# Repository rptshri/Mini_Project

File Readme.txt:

http://www.me.umn.edu/education/undergraduate/writing/How-to-write-a-Design-Report.pdf

ARDUINO DESIGN:
https://www.allaboutcircuits.com/technical-articles/understanding-arduino-uno-hardware-design/

SG90 http://www.ee.ic.ac.uk/pcheung/teaching/DE1_EE/stores/sg90_datasheet.pdf

MG995 https://www.towerpro.com.tw/product/mg995/

BLUETOOTH MODULE  https://howtomechatronics.com/tutorials/arduino/arduino-and-hc-05-bluetooth-module-tutorial/

MDF https://en.wikipedia.org/wiki/Medium-density_fibreboard

3D Design https://www.tinkercad.com/things/dJmnHaHhOIF-grand-snaget-amur/edit

Materials https://www.3dhubs.com/knowledge-base/pla-vs-abs-whats-difference 

MDF Plywood difference https://www.livspace.com/magazine/mdf-vs-plywood-comparison/

1. Project report *
2. Imperial Sheet *
3. Project hardware  *   
4. Project log book *
5. altium pcb file 
6. Proteus simulation file *
7. Pcb vs schematic.  8.Code

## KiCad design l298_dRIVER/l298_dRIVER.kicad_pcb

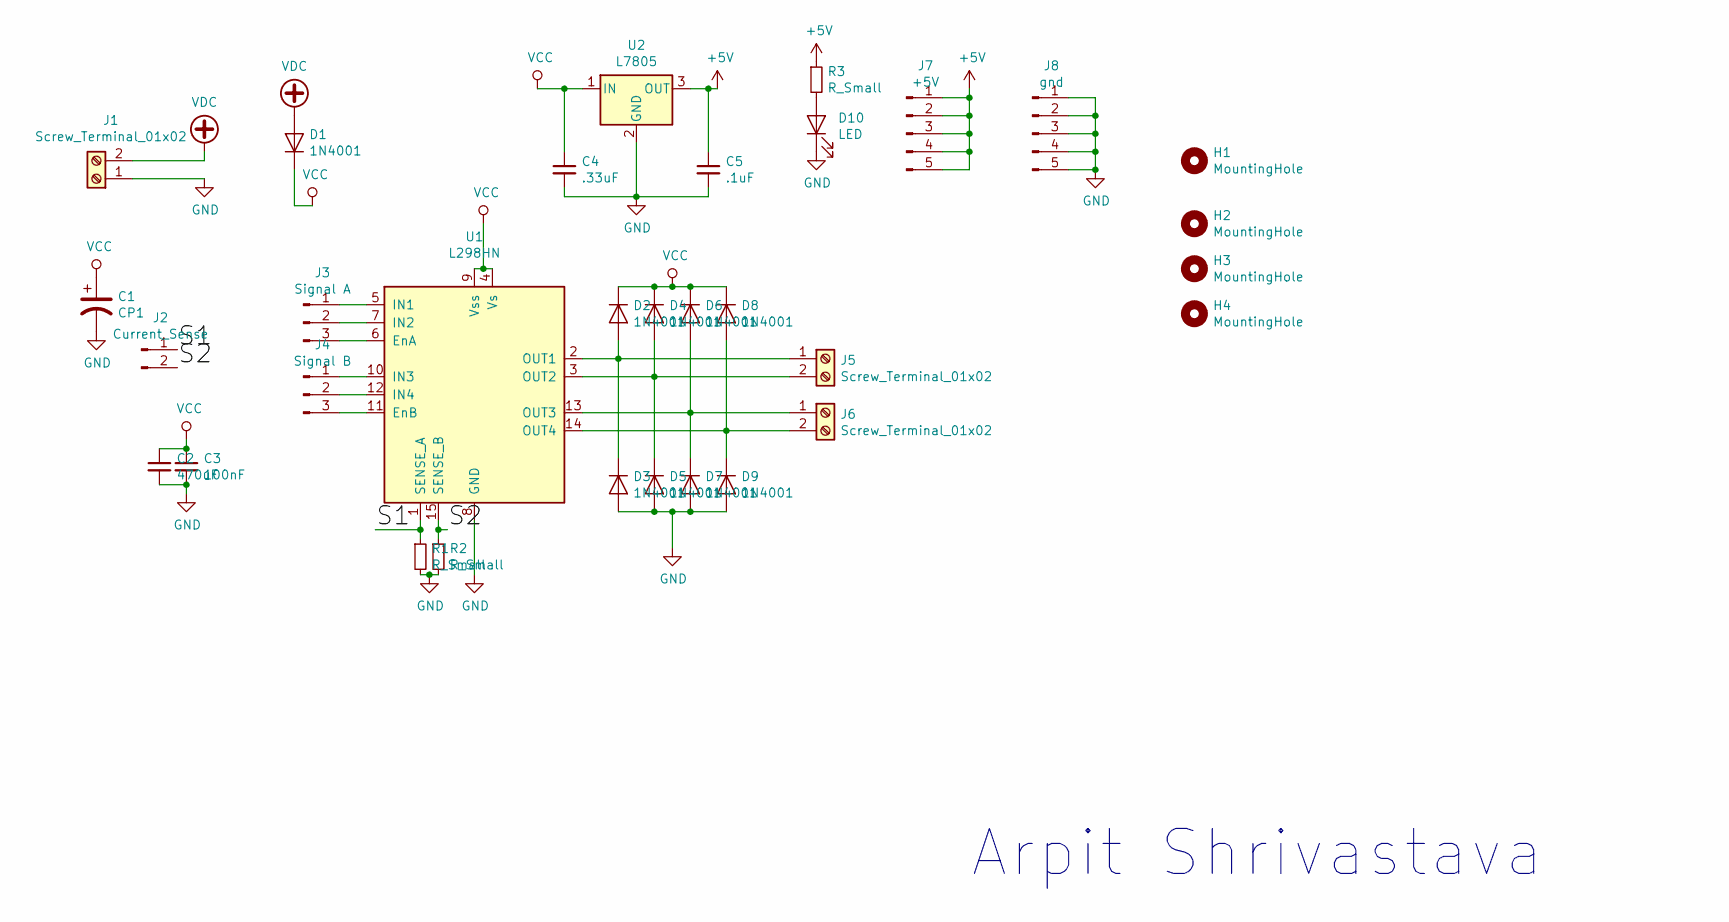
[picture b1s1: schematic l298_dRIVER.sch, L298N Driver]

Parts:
C1: CP1; CP_Radial_D10.0mm_P2.50mm_P5.00mm
C2: 470uF; C_Disc_D3.4mm_W2.1mm_P2.50mm
C3: 100nF; C_Disc_D3.4mm_W2.1mm_P2.50mm
C4: .33uF; C_Disc_D3.4mm_W2.1mm_P2.50mm
C5: .1uF; C_Disc_D3.4mm_W2.1mm_P2.50mm
D1, D2, D3, D4, D5, D6, D7, D8, D9: 1N4001; D_DO-41_SOD81_P7.62mm_Horizontal
D10: LED; LED_D3.0mm
H1, H2, H3, H4: MountingHole; MountingHole_3.2mm_M3_DIN965
J1, J5, J6: Screw_Terminal_01x02; TerminalBlock_Altech_AK300-2_P5.00mm
J2: Current_Sense; PinHeader_1x02_P2.54mm_Vertical
J3: Signal A; PinHeader_1x03_P2.54mm_Vertical
J4: Signal B; PinHeader_1x03_P2.54mm_Vertical
J7: +5V; PinHeader_1x05_P2.54mm_Vertical
J8: gnd; PinHeader_1x05_P2.54mm_Vertical
R1, R2, R3: R_Small; R_Axial_DIN0207_L6.3mm_D2.5mm_P7.62mm_Horizontal
U1: L298HN; TO-220-15_P2.54x2.54mm_StaggerOdd_Lead4.58mm_Vertical
U2: L7805; TO-220-3_Vertical

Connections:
+5V: C5.1, J7.1, J7.2, J7.3, J7.4, J7.5, R3.1, U2.3 (OUT)
/S1: J2.1, R1.1, U1.1 (SENSE_A)
/S2: J2.2, R2.1, U1.15 (SENSE_B)
GND: C1.2, C2.2, C3.2, C4.2, C5.2, D3.2 (A), D5.2 (A), D7.2 (A), D9.2 (A), D10.1 (K), J1.1, J8.1, J8.2, J8.3, J8.4, J8.5, R1.2, R2.2, U1.8 (GND), U2.2 (GND)
unnamed: D2.2 (A), D3.1 (K), J5.1, U1.2 (OUT1)
unnamed: D4.2 (A), D5.1 (K), J5.2, U1.3 (OUT2)
unnamed: D6.2 (A), D7.1 (K), J6.1, U1.13 (OUT3)
unnamed: D8.2 (A), D9.1 (K), J6.2, U1.14 (OUT4)
unnamed: D10.2 (A), R3.2
unnamed: J3.1, U1.5 (IN1)
unnamed: J3.2, U1.7 (IN2)
unnamed: J3.3, U1.6 (EnA)
unnamed: J4.1, U1.10 (IN3)
unnamed: J4.2, U1.12 (IN4)
unnamed: J4.3, U1.11 (EnB)
VCC: C1.1, C2.1, C3.1, C4.1, D1.1 (K), D2.1 (K), D4.1 (K), D6.1 (K), D8.1 (K), U1.4 (Vs), U1.9 (Vss), U2.1 (IN)
VDC: D1.2 (A), J1.2

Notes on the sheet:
Arpit Shrivastava

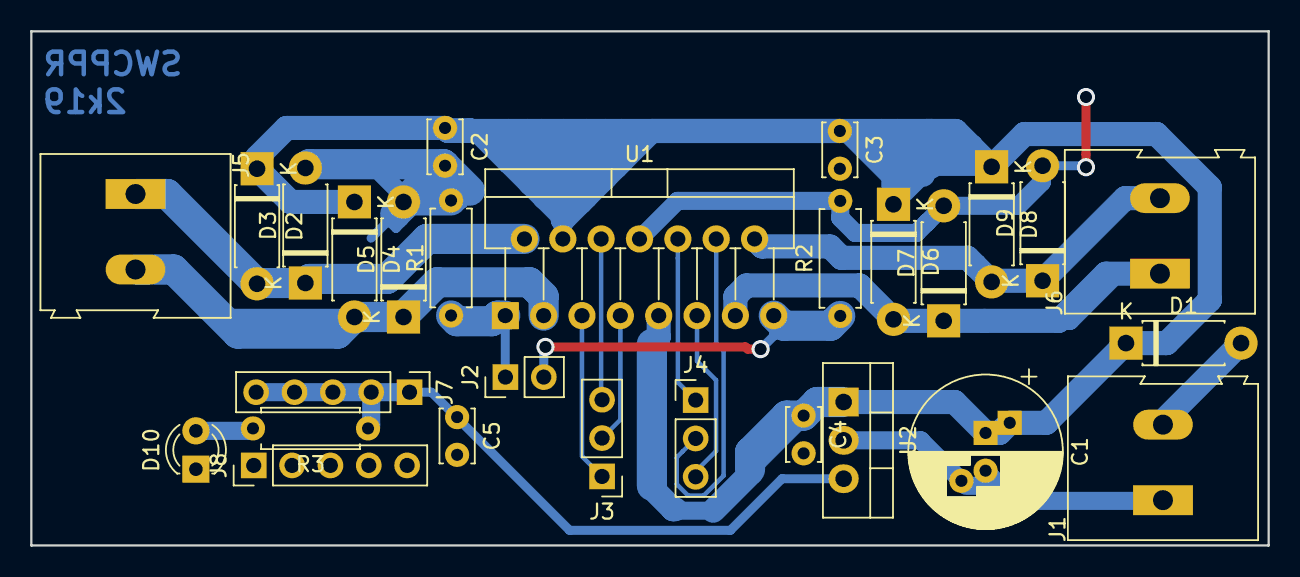
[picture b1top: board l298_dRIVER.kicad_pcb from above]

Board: 2 copper layers, 82.0 x 34.1 mm, 32 parts (0 on the bottom side), 17 nets.

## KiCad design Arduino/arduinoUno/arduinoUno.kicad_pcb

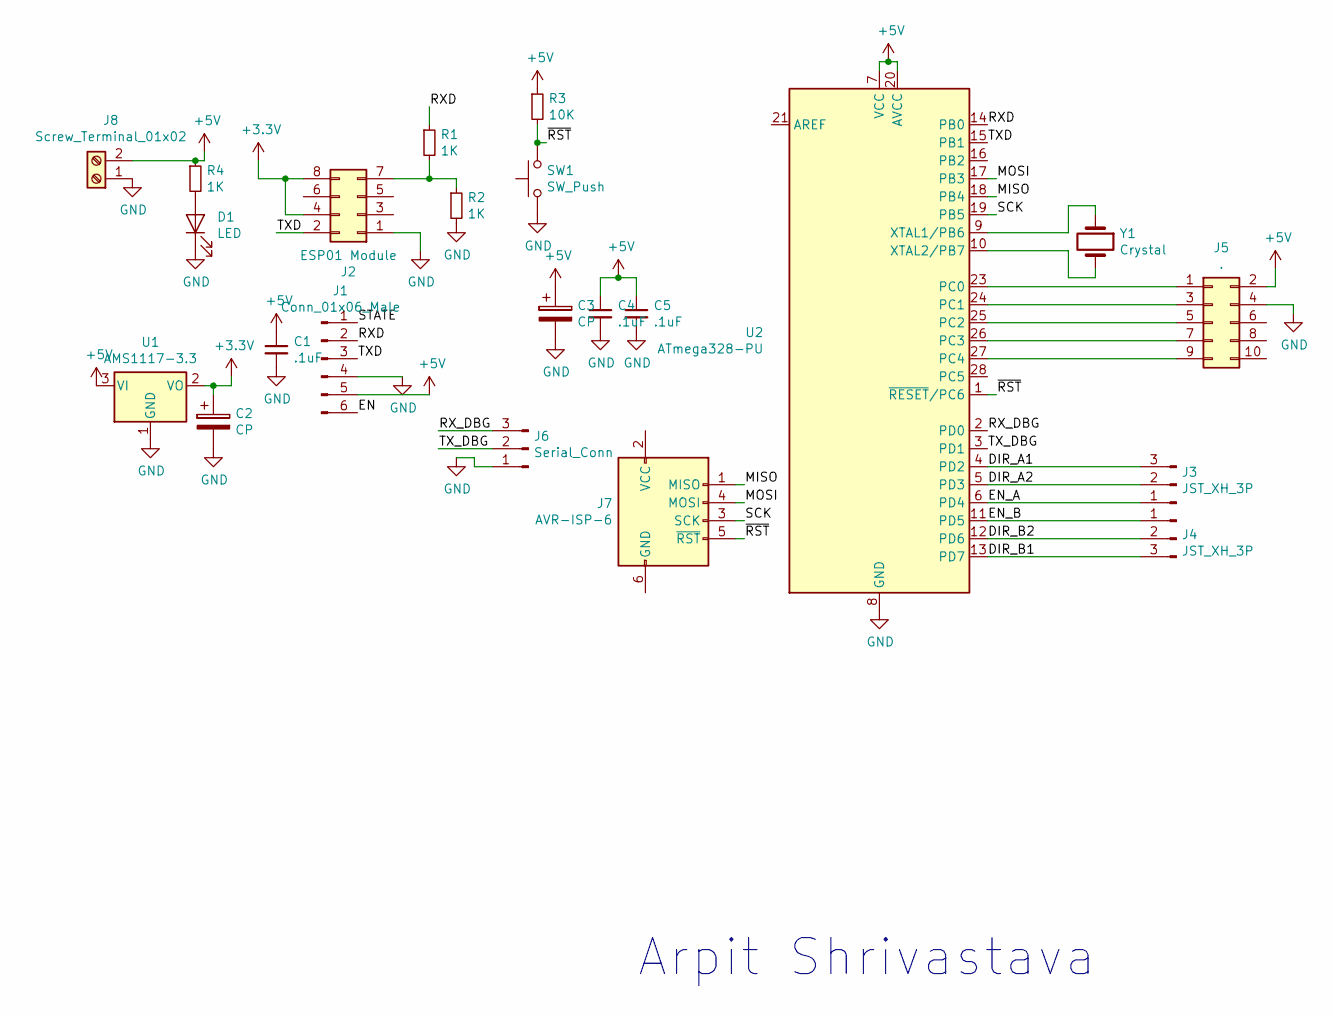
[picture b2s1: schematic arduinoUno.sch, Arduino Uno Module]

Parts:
C1, C4, C5: .1uF; C_Disc_D3.0mm_W1.6mm_P2.50mm
C2, C3: CP; CP_Radial_D10.0mm_P2.50mm_P5.00mm
D1: LED; LED_D3.0mm
J1: Conn_01x06_Male; PinSocket_1x06_P2.54mm_Vertical
J2: ESP01 Module; PinHeader_2x04_P2.54mm_Vertical
J3, J4: JST_XH_3P; JST_XH_B03B-XH-A_1x03_P2.50mm_Vertical
J5: .; IDC-Header_2x05_P2.54mm_Vertical
J6: Serial_Conn; PinHeader_1x03_P2.54mm_Vertical
J7: AVR-ISP-6; PinHeader_2x03_P2.54mm_Vertical
J8: Screw_Terminal_01x02; TerminalBlock_Altech_AK300-2_P5.00mm
R1, R2, R4: 1K; R_Axial_DIN0207_L6.3mm_D2.5mm_P7.62mm_Horizontal
R3: 10K; R_Axial_DIN0207_L6.3mm_D2.5mm_P7.62mm_Horizontal
SW1: SW_Push; SW_PUSH_6mm
U1: AMS1117-3.3; SOT-223-3_TabPin2
U2: ATmega328-PU; DIP-28_W7.62mm_Socket_LongPads
Y1: Crystal; Crystal_HC18-U_Vertical

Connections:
+3V3: C2.1, J2.4, J2.8, U1.2 (VO)
+5V: C1.1, C3.1, C4.1, C5.1, J1.5, J5.2, J8.2, R3.1, R4.1, U1.3 (VI), U2.7 (VCC), U2.20 (AVCC)
/DIR_A1: J3.3, U2.4 (PD2)
/DIR_A2: J3.2, U2.5 (PD3)
/DIR_B1: J4.3, U2.13 (PD7)
/DIR_B2: J4.2, U2.12 (PD6)
/EN: J1.6
/EN_A: J3.1, U2.6 (PD4)
/EN_B: J4.1, U2.11 (PD5)
/MISO: J7.1 (MISO), U2.18 (PB4)
/MOSI: J7.4 (MOSI), U2.17 (PB3)
/RXD: J1.2, R1.1, U2.14 (PB0)
/RX_DBG: J6.3, U2.2 (PD0)
/SCK: J7.3 (SCK), U2.19 (PB5)
/STATE: J1.1
/TXD: J1.3, J2.2, U2.15 (PB1)
/TX_DBG: J6.2, U2.3 (PD1)
/~RST: J7.5 (~RST), R3.2, SW1.2, U2.1 (~RESET~/PC6)
GND: C1.2, C2.2, C3.2, C4.2, C5.2, D1.1 (K), J1.4, J2.1, J5.4, J6.1, J8.1, R2.2, SW1.1, U1.1 (GND), U2.8 (GND), U2.22 (GND)
unnamed: D1.2 (A), R4.2
unnamed: J2.7, R1.2, R2.1
unnamed: J5.1, U2.23 (PC0)
unnamed: J5.3, U2.24 (PC1)
unnamed: J5.5, U2.25 (PC2)
unnamed: J5.7, U2.26 (PC3)
unnamed: J5.9, U2.27 (PC4)
unnamed: U2.9 (XTAL1/PB6), Y1.1
unnamed: U2.10 (XTAL2/PB7), Y1.2

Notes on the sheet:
Arpit Shrivastava

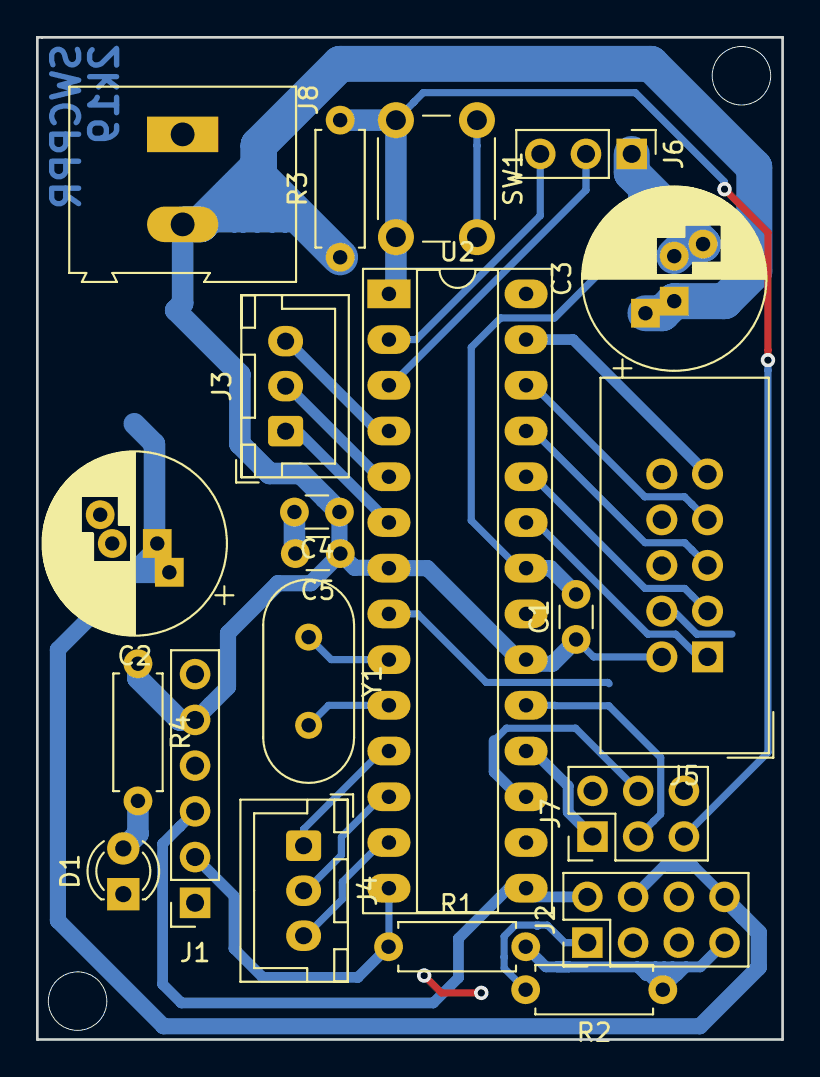
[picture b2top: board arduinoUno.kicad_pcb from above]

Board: 2 copper layers, 41.4 x 55.7 mm, 22 parts (1 on the bottom side), 26 nets.

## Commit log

2019-03-31 Sunday_commit
2019-03-31 added bluetooth codes
2019-03-31 added sample report
2019-03-31 uploaded bluetooth code
2019-04-01 added Uno board
2019-04-07 report added
2019-04-09 project_synopsys added
2019-04-09 Update project_synopsys
2019-04-09 Boards Aded
2019-04-11 embedded_report pdf update
2019-04-11 uploaded my folder
2019-04-11 organized
2019-04-11 added intro and background
2019-04-12 Uploaded my report work
2019-04-20 ipdate
2019-04-20 asfd
2019-04-20 Create MG 995 & comparison.docx
    added mg995 &
    comparison
2019-04-20 links
2019-04-21 stepper test code
2019-04-22 NIGHTLY
2019-04-23 PDF FOR PRINTING ADDED
2019-04-23 right and left turn tested OK code
2019-04-23 junction counting working like charm
2019-04-24 Motor driver cmp
2019-04-24 mdf diff
2019-04-24 duggu
2019-04-24 datatsheet motor
2019-04-24 CALC
2019-04-24 added sketch
2019-04-24 final report added
2019-04-30 finally done with Everything
2020-05-25 [ImgBot] Optimize images
    *Total -- 1,580.47kb -> 1,108.57kb (29.86%)
    /Documents/motor_driver.png -- 67.43kb -> 21.06kb (68.76%)
    /l298_dRIVER/l298_dRIVER-Edge.Cuts.svg -- 1.02kb -> 0.52kb (49.14%)
    /l298_dRIVER/l298_dRIVER-F.Cu.svg -- 50.30kb -> 26.43kb (47.44%)
    /Arduino/arduinoUno/arduinoUno-B.Cu.svg -- 90.40kb -> 62.00kb (31.41%)
    /l298_dRIVER/l298_dRIVER-B.Cu.svg -- 615.80kb -> 424.45kb (31.07%)
